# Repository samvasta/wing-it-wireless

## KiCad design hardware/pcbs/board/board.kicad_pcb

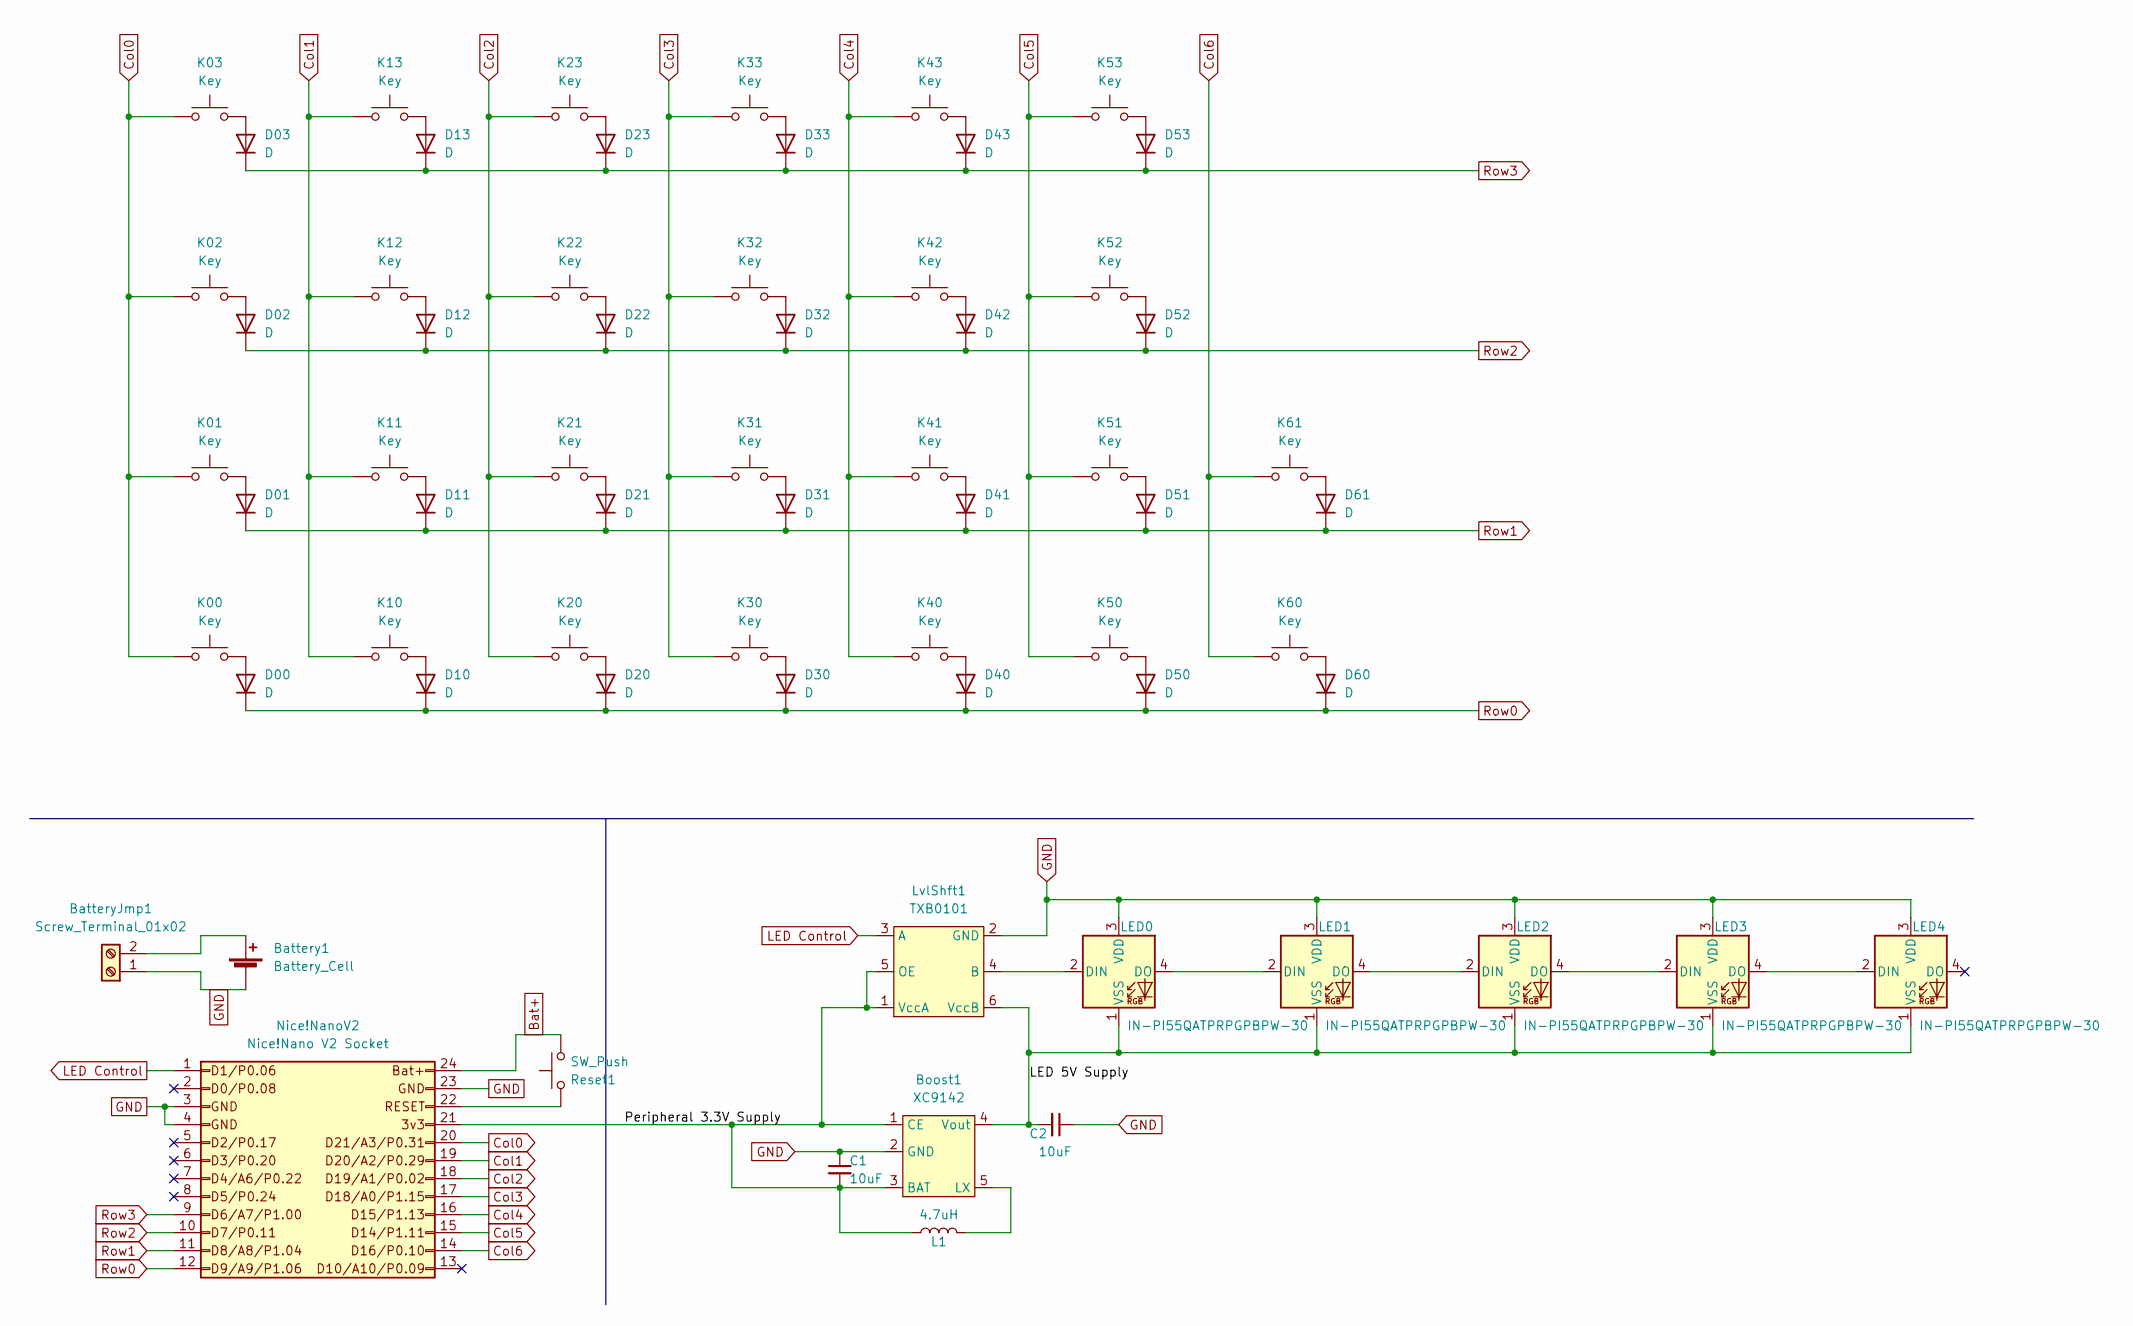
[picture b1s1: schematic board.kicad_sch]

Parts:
Battery1: Battery_Cell; BatteryHolder_Keystone_1088_1xAA
BatteryJmp1: Screw_Terminal_01x02; TerminalBlock_bornier-2_P5.08mm
Boost1: XC9142; SOT-25-5
C1, C2: 10uF; C_0805_2012Metric_Pad1.18x1.45mm_HandSolder
D00, D01, D02, D03, D10, D11, D12, D13, D20, D21, D22, D23, D30, D31, D32, D33, D40, D41, D42, D43, D50, D51, D52, D53, D60, D61: D; D_MiniMELF_Handsoldering_Shorter_Pads_DoubleSided
K00, K01, K02, K03, K10, K11, K12, K13, K20, K21, K22, K23, K30, K31, K32, K33, K40, K41, K42, K43, K50, K51, K52, K53, K60, K61: Key; Kailh_socket_reversible
L1: 4.7uH; L_0805_2012Metric_Pad1.15x1.40mm_HandSolder
LED0, LED1, LED2, LED3, LED4: IN-PI55QATPRPGPBPW-30; LED_Inolux_IN-PI554FCH_PLCC4_5.0x5.0mm_P3.2mm
LvlShft1: TXB0101; SOT-23-6_Handsoldering
Nice!NanoV2: Nice!Nano V2 Socket; Nice!NanoSocket_Reversible
Reset1: SW_Push; SW_PUSH_6mm

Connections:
/LED 5V Supply: Boost1.4 (Vout), C2.2, LED0.1 (VSS), LED1.1 (VSS), LED2.1 (VSS), LED3.1 (VSS), LED4.1 (VSS), LvlShft1.6 (VccB); also elsewhere on the board
/Peripheral 3.3V Supply: Boost1.1 (CE), Boost1.3 (BAT), C1.2, L1.1, LvlShft1.1 (VccA), LvlShft1.5 (OE), Nice!NanoV2.21
Bat+: Nice!NanoV2.24, Reset1.2
Col0: K00.1, K01.1, K02.1, K03.1, Nice!NanoV2.20
Col1: K10.1, K11.1, K12.1, K13.1, Nice!NanoV2.19
Col2: K20.1, K21.1, K22.1, K23.1, Nice!NanoV2.18
Col3: K30.1, K31.1, K32.1, K33.1, Nice!NanoV2.17
Col4: K40.1, K41.1, K42.1, K43.1, Nice!NanoV2.16
Col5: K50.1, K51.1, K52.1, K53.1, Nice!NanoV2.15
Col6: K60.1, K61.1, Nice!NanoV2.14
GND: Battery1.2 (-), BatteryJmp1.1, Boost1.2 (GND), C1.1, C2.1, LED0.3 (VDD), LED1.3 (VDD), LED2.3 (VDD), LED3.3 (VDD), LED4.3 (VDD), LvlShft1.2 (GND), Nice!NanoV2.3, Nice!NanoV2.4, Nice!NanoV2.23; also elsewhere on the board
LED Control: LvlShft1.3 (A), Nice!NanoV2.1
unnamed 12: Battery1.1 (+), BatteryJmp1.2; also elsewhere on the board
unnamed: Boost1.5 (LX), L1.2
unnamed: D00.2 (A), K00.2
unnamed: D01.2 (A), K01.2
unnamed: D02.2 (A), K02.2
unnamed: D03.2 (A), K03.2
unnamed: D10.2 (A), K10.2
unnamed: D11.2 (A), K11.2
unnamed: D12.2 (A), K12.2
unnamed: D13.2 (A), K13.2
unnamed: D20.2 (A), K20.2
unnamed: D21.2 (A), K21.2
unnamed: D22.2 (A), K22.2
unnamed: D23.2 (A), K23.2
unnamed: D30.2 (A), K30.2
unnamed: D31.2 (A), K31.2
unnamed: D32.2 (A), K32.2
unnamed: D33.2 (A), K33.2
unnamed: D40.2 (A), K40.2
unnamed: D41.2 (A), K41.2
unnamed: D42.2 (A), K42.2
unnamed: D43.2 (A), K43.2
unnamed: D50.2 (A), K50.2
unnamed: D51.2 (A), K51.2
unnamed: D52.2 (A), K52.2
unnamed: D53.2 (A), K53.2
unnamed: D60.2 (A), K60.2
unnamed: D61.2 (A), K61.2
unnamed 40: LED0.2 (DIN), LvlShft1.4 (B); also elsewhere on the board
unnamed 41: LED0.4 (DO), LED1.2 (DIN); also elsewhere on the board
unnamed 42: LED1.4 (DO), LED2.2 (DIN); also elsewhere on the board
unnamed 43: LED2.4 (DO), LED3.2 (DIN); also elsewhere on the board
unnamed 44: LED3.4 (DO), LED4.2 (DIN); also elsewhere on the board
unnamed: Nice!NanoV2.22, Reset1.1
Row0: D00.1 (K), D10.1 (K), D20.1 (K), D30.1 (K), D40.1 (K), D50.1 (K), D60.1 (K), Nice!NanoV2.12
Row1: D01.1 (K), D11.1 (K), D21.1 (K), D31.1 (K), D41.1 (K), D51.1 (K), D61.1 (K), Nice!NanoV2.11
Row2: D02.1 (K), D12.1 (K), D22.1 (K), D32.1 (K), D42.1 (K), D52.1 (K), Nice!NanoV2.10
Row3: D03.1 (K), D13.1 (K), D23.1 (K), D33.1 (K), D43.1 (K), D53.1 (K), Nice!NanoV2.9

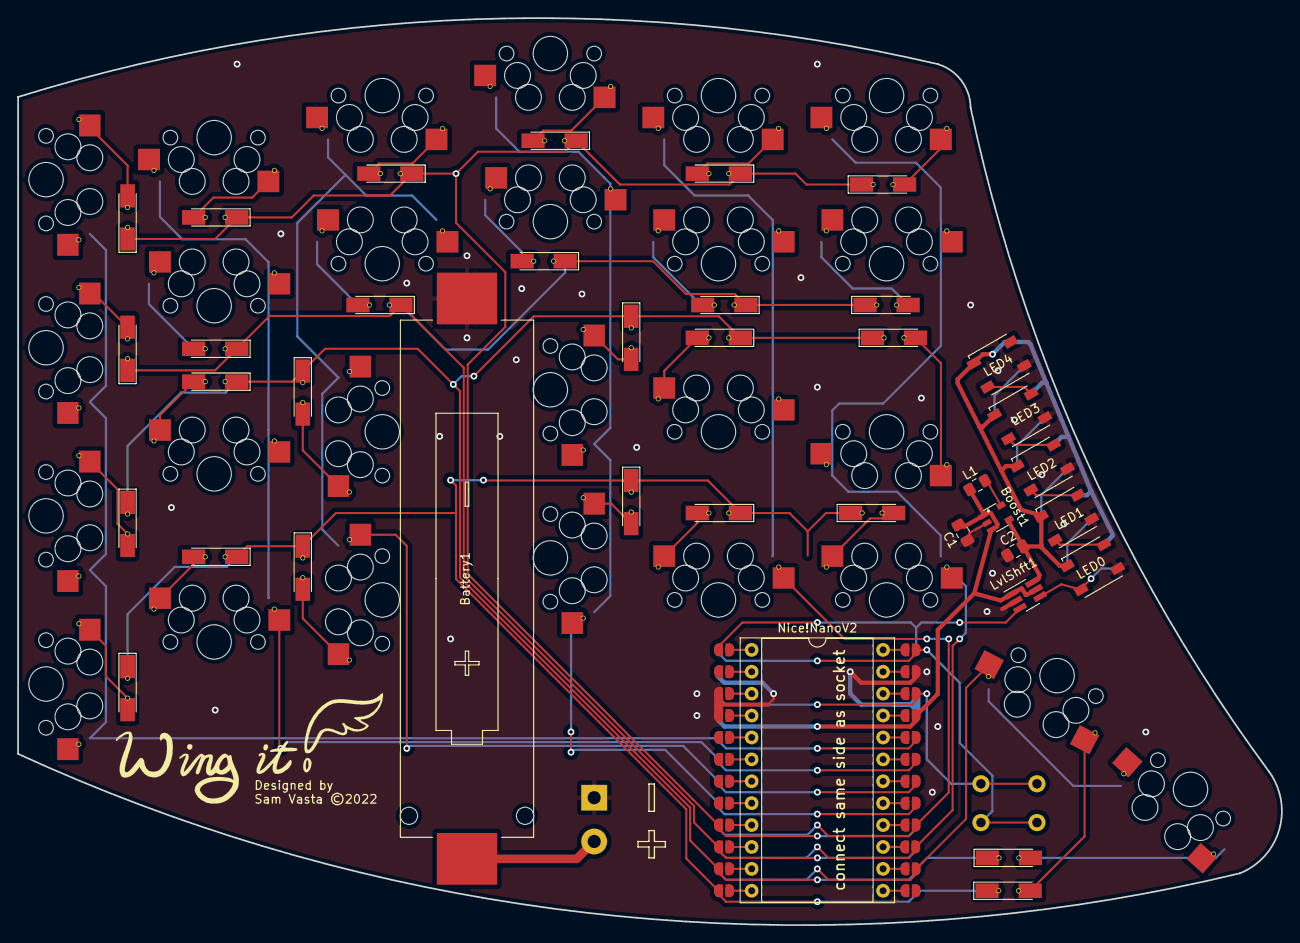
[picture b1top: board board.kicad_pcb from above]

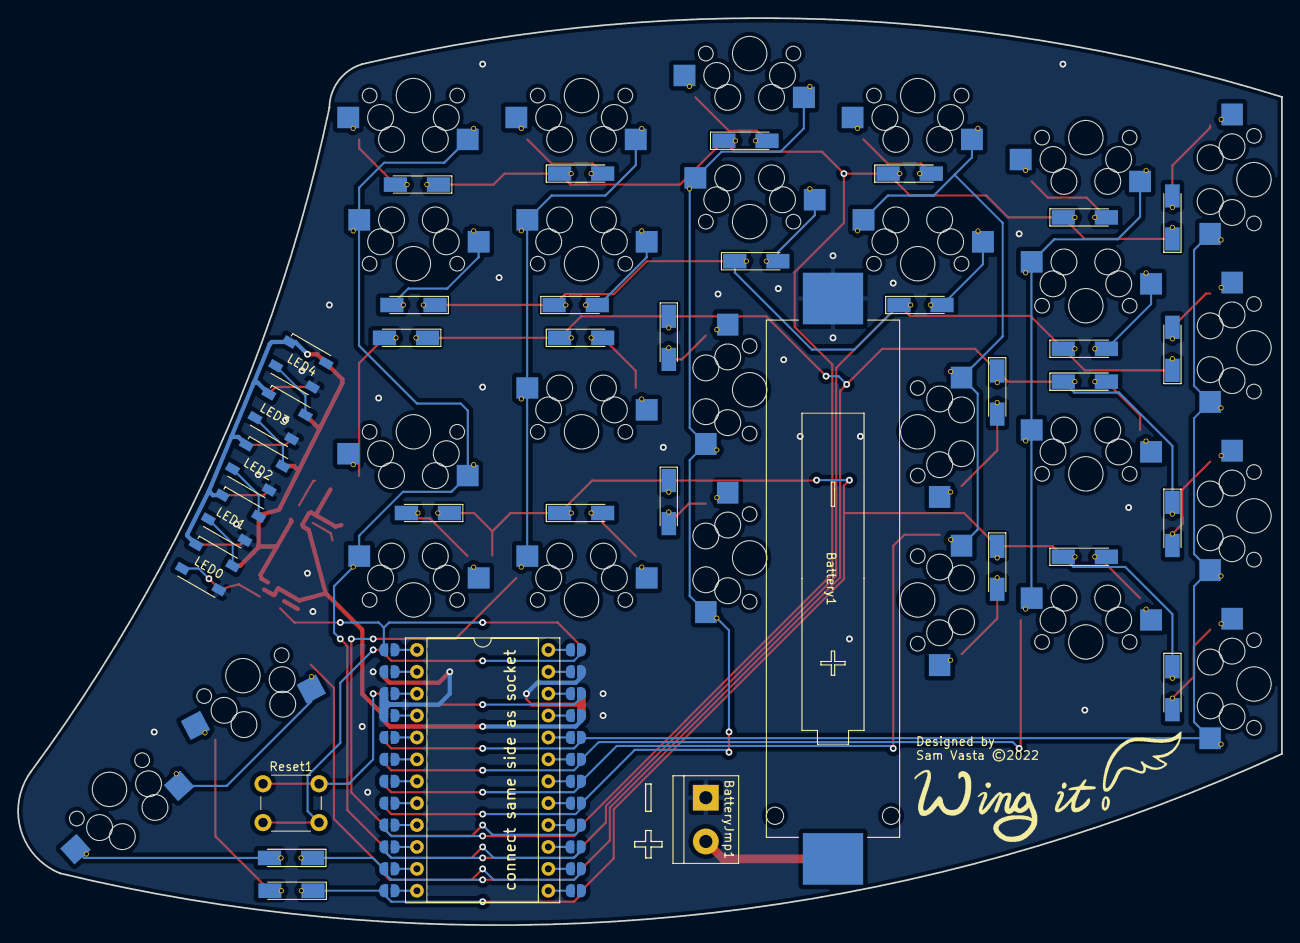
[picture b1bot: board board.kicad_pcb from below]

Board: 2 copper layers, 146.6 x 105.2 mm, 72 parts (8 on the bottom side), 50 nets.

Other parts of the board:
Battery1#2: Battery_Cell; BatteryHolder_Keystone_1088_1xAA
LED0#2, LED1#2, LED2#2, LED3#2, LED4#2: IN-PI55QATPRPGPBPW-30; LED_Inolux_IN-PI554FCH_PLCC4_5.0x5.0mm_P3.2mm

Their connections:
/LED 5V Supply: LED0#2.1 (VSS), LED1#2.1 (VSS), LED2#2.1 (VSS), LED3#2.1 (VSS), LED4#2.1 (VSS); also elsewhere on the board
GND: Battery1#2.2 (-), LED0#2.3 (VDD), LED1#2.3 (VDD), LED2#2.3 (VDD), LED3#2.3 (VDD), LED4#2.3 (VDD); also elsewhere on the board
unnamed 12: Battery1#2.1 (+); also elsewhere on the board
unnamed 40: LED0#2.2 (DIN); also elsewhere on the board
unnamed 41: LED0#2.4 (DO), LED1#2.2 (DIN); also elsewhere on the board
unnamed 42: LED1#2.4 (DO), LED2#2.2 (DIN); also elsewhere on the board
unnamed 43: LED2#2.4 (DO), LED3#2.2 (DIN); also elsewhere on the board
unnamed 44: LED3#2.4 (DO), LED4#2.2 (DIN); also elsewhere on the board

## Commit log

2022-05-18 added top plate
2022-05-20 pcb v1
2022-05-22 updates to pcb and case
2022-05-22 update kicad libs
2022-07-03 updates?
2022-07-03 pcb updates
2022-07-03 again
2022-07-26 worked on 3d files
2023-05-08 stale updates from v1
2023-05-08 pdfs
2023-05-27 case STLs

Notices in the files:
hardware/pcbs/board/board.kicad_pcb:
Designed by
Sam Vasta ©2022
